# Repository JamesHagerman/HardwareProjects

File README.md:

HardwareProjects
================

This is a repo to hold my Processing, Arduino, and PCB design projects.

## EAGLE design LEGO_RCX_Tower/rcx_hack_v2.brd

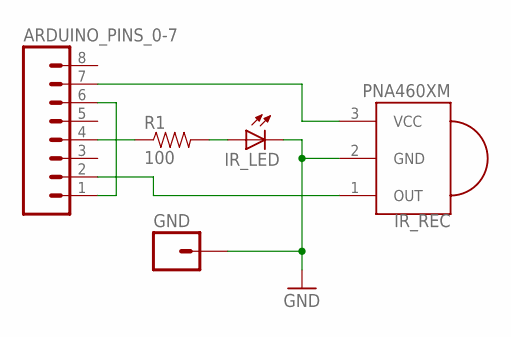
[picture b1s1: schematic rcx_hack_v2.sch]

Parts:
ARDUINO_PINS_0-7: M08LOCK; 1X08_LOCK
GND: 1X01_LONGPAD
IR_LED: LED5MM
IR_REC: PNA460XM
R1: 100; AXIAL-0.3

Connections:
GND: GND.1, IR_LED.K (C), IR_REC.2 (GND)
unnamed: ARDUINO_PINS_0-7.2, IR_REC.1 (OUT)
unnamed: IR_LED.A, R1.P$2 (2)
unnamed: ARDUINO_PINS_0-7.4, R1.P$1 (1)
unnamed: ARDUINO_PINS_0-7.7, IR_REC.3 (VCC)
unnamed: ARDUINO_PINS_0-7.1, ARDUINO_PINS_0-7.6

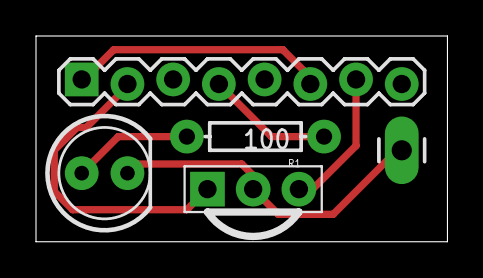
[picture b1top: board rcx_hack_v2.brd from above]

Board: 2 copper layers, 22.9 x 11.4 mm, 5 parts (0 on the bottom side), 6 nets.

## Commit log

2013-07-29 Adding the mpu-9150 project
2013-08-02 Adding the Sensatron 2013 project to github for the friends
2013-08-02 Adding more light control methods
2013-08-02 Rotating the view and fixing some things.
2013-08-02 Moving 3d display to a seperate workspace so we can start building out some UI and preview stuff.
2013-08-04 Adding a few more projects. Fridge fix in arduino and pic12f683. Parallel ROM WRiter Shield uploader and firmware. Circular Animation in processing.
2013-08-04 Adding video display.
2013-08-05 Fixing the camera color polling. Finally.
2013-08-05 Updating things.
2013-08-05 More work on the lights. switching out the camera again.
2013-08-09 Finially getting the circle animation into the lighting rig.
2013-08-15 A bunch of updates.
2013-08-16 Adding path for driver location.
2013-08-16 Adding try catch block for the camera setup.
2013-08-16 Moving some things around.
2013-08-17 Updating position of display stuff.
2013-08-17 Deleting things...
2013-08-17 Fixing a merge conflict. Pull first james...
2013-08-18 Adding some example code and starting a rebuild of the Sensatron code to support multiple animations in the Disorient Pyramid Animation format.
2013-08-18 Porting original circle animation code to the new class based system.
2013-08-18 Adding TCL Control and radial control classes and implementing them correctly.
2013-08-18 Adding the 3d light display to the project.
2013-08-18 Adding camera support.
2013-08-18 Cleaning up some comments to make the next step of adding animations a LOT easier.
2013-08-18 Adding build-tmp directories to gitignore so i can develop with sublime text.
2013-08-18 Starting to add gyro box input to the project for awesome interactive art.
2013-08-19 Making the gyro work as an input into the lighting rig
2013-08-20 Updating some stuff in the lighting rig to make the gyro code work better. Adding an animation builder sketch that should make animations easier to create.
2013-08-23 Adding button functionality timeout.
2013-08-23 Adding button functionality on pin 2
2013-08-23 Making the led blink a bunch when the button is pressed.
2013-08-24 Adding some changes before I leave.
2013-08-24 Making more changes for gyro. from the mac mini...
2013-08-24 One more update from the mac mini...
2013-08-26 Fixing the remap and setting up a fake mouse movement system. Also checking in a bunch of junk for the gyro. It is probably broken.
2013-12-06 Finally remembering to check in all that code I wrote at burning man.... and adding the XMas tree LED project code starting point.
2013-12-06 Starting to comment out the things we don't need and adding the ability to run the app without all the hardware hooked up.
2013-12-06 Adding the dual kinect code to the repo for integration with the Sensatron lighting rig code for XMasBrights project.
2013-12-06 After making a bunch of much needed cleanup, this code should clearly be project agnostic. It is now just the TCL Lighting Rig. Animations themselves will be project specific. And the mapping and lig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
2013-12-06 Moving all of the sensatron or tcl related processing code into a subfolder.
2013-12-06 Moving old versions of the lighting rig into subfolders so the latest version is clear.
2013-12-06 deleting moved versions...
2013-12-06 Starting to add multiple kinect support to the TCL Lighting Rig.
2013-12-06 Adding flob tracking to the KinectManager class so we can get at more useable vector based data.
2013-12-06 Adding a readme to the TCL Lighting Rig project.
2013-12-06 More readme...
2013-12-08 Adding the UBW32 starter project to the repoistory. I am sick of loo looking this shit up every time I want to do a project.
2013-12-10 Refactoring the animation code so we can integrate Kinect data into animations more easily.
2013-12-10 Moving even more stuff arround so we can finally get down to working in a nice clean animation-centric environment.
2013-12-10 Moving all of the radial realted code into a single class so we can abstract more of the display code for new projects.
2013-12-10 Moving all the radial mapping array stuff over to the RadialControll class as well. What a mess...
2013-12-10 Cleaning up just a little more before I go home...
2013-12-11 Adding the start of a spiral map. And then dropping it on the floor for another method of getting physical mapping points into the system based on mouseclicks.
2013-12-11 Adding the ability to click on the screen to set where each light gets its color from. This is a hack for now. We should be able to generate CSV files that will then be able to be used for pixel mapp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
2013-12-11 Adding a circular csv file to the project so we actually have a sane data set...
2013-12-11 Starting to add kinect hardware input management.
2013-12-12 Finally getting all of the rest of the basic kinect control work into the repo. Next thing will need to be a better depth filter...
2013-12-12 I hate this fucking library.
2013-12-12 Adding my own damn depth field to get past all the stupidness inside of the flob library.
2013-12-12 Pushing all of the cleaned up kinect depth filtering into use now and fixing the actual display portion of the app. Getting a LOT closer now... Just need to figure out how to map the data into a usea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
2013-12-12 Finally down to animations...
2013-12-12 Adding the modified kinect library to the project.
2013-12-12 Adding the TCL library too since no one updates their damn libraries to universal...
2013-12-12 Adding the tree work to the repo.
2013-12-12 saving stuff for the tree.
2013-12-21 Adding a final update to the locations.csv for the xmas brights project. Copying the UBW32 starter project over to a new directory to start FINALLY working on that damn synth project.
2013-12-21 Renaming the synth starter project. Adding comments laying out what the project will need to include in the future. Adding a bunch of useful SPI stuff to the project. We could probably make a README.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
2014-01-07 Adding working SPI methods to the synth starter project. Still maxing out at about 37kHz even at 24MHz SPI rate... we are not gonna be able to make a clean synth outta this system... I2S is next.
2014-01-08 Updating the pic32 synth code to support ADC read and DAC write operations over SPI. Next step is adding the Wolson SPI controls and I2S PCM generation code. Maybe an SD card reader too...
2014-01-13 Turning off JTAG to get back some IO pins.
2014-01-13 Adding the LEGO RCX Tower code to the project. Finally, a way to communicate with the RCX again. Circuit coming soon.
2014-02-05 Adding some changes to the synth starter project.
2014-02-19 Adding some comments and adding a fixed Eagle schematic and board to the RCX project. Playing with something in the synth starter project.
2014-11-19 Updating the UBS32 code to work with the pic32mx450f256l
2015-02-08 Adding my parts libraries to the repo so I can use them on other machines.
2015-05-01 Adding the red keyboard code to the repo. Adding the pic12f683 work to the repo.
2015-05-01 Updating the Red Keyboard project so that it actually spits out voltages CLOSE to what they should be. I need a tuning function...
2015-05-07 Moving code around so that it is a little more abstracted. Now I can think about the tuning mode more clearly.
2015-05-07 Starting to add EEPROM storage of the tuning values.
2015-05-07 Writing a uint16_t eeprom getter and setter. Reorganizing some of the other code so that it makes a bit more sense using these new methods.
2015-05-08 Finalizing the read and write functions from eeprom. This thing should be good to go. Once the power is done at least.
2015-05-08 Finally building out the analogRead function on the pic12f683 that I should have done ages ago...

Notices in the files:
parts and their libraries:
SparkFun-Connectors: Licensing: CC v3.0 Share-Alike You are welcome to use this library for commercial purposes.
